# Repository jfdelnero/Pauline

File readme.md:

# Pauline FDC

Pauline is an open-source, powerful, universal and simple to use tool that will allow you to scan with
precision the content of the magnetic disks you want to archive, regardless of their format.

Pauline is a tool developed within the association La Ludothe`que Française, in partnership with
the associations Game Preservation Society located in Japan, and MO5.COM located in France.

https://www.laludotheque.fr/projets-en-cours/preservation-des-disquettes-pauline/

### Features

 - Based on the FPGA DE10-nano board.
 - Supports 8",5"1/4 3"1/2, 3" Shugart and PC drives.
 - Supports Apple II floppy drives.
 - Supports Macintosh floppy drives.
 - Capture resolution : 50 MHz or 25 MHz
 - Can capture up to 16 channels.
 - Can perfectly simulate/emulate up to 4 Shugart/PC drives (Mac/Apple II support planned)
 - Hardware drives emulation - No software or flash latency.
 - Based on Linux.
 - Embedded SSH / HTTP / FTP / Windows share servers.
 - USB and Ethernet connection.
 - Embedded web server to control the unit. No software to install on the computer.
 - Real time track analysis and display.

 And many more !

### How to build it ?

This use the HxCFloppyEmulator software repository as submodule so the proper way to clone the project is :

```c
git clone --recursive https://github.com/jfdelnero/Pauline.git
```

To update the repository :

```c
git pull
git submodule update --init --recursive
```

-------------------------------------------------------------------------------

HxC Floppy Emulator project

Generic/universal floppy disk drive emulators

Copyright (C) 2006-2026  Jean-François DEL NERO / HxC2001

Email :    hxc2001(at)hxc2001.com

Website :  https://hxc2001.com
           http://hxc2001.free.fr/floppy_drive_emulator

Forum :    https://torlus.com/floppy/forum

Facebook : https://www.facebook.com/groups/hxc2001/

Twitter :  https://twitter.com/jfdelnero

-------------------------------------------------------------------------------

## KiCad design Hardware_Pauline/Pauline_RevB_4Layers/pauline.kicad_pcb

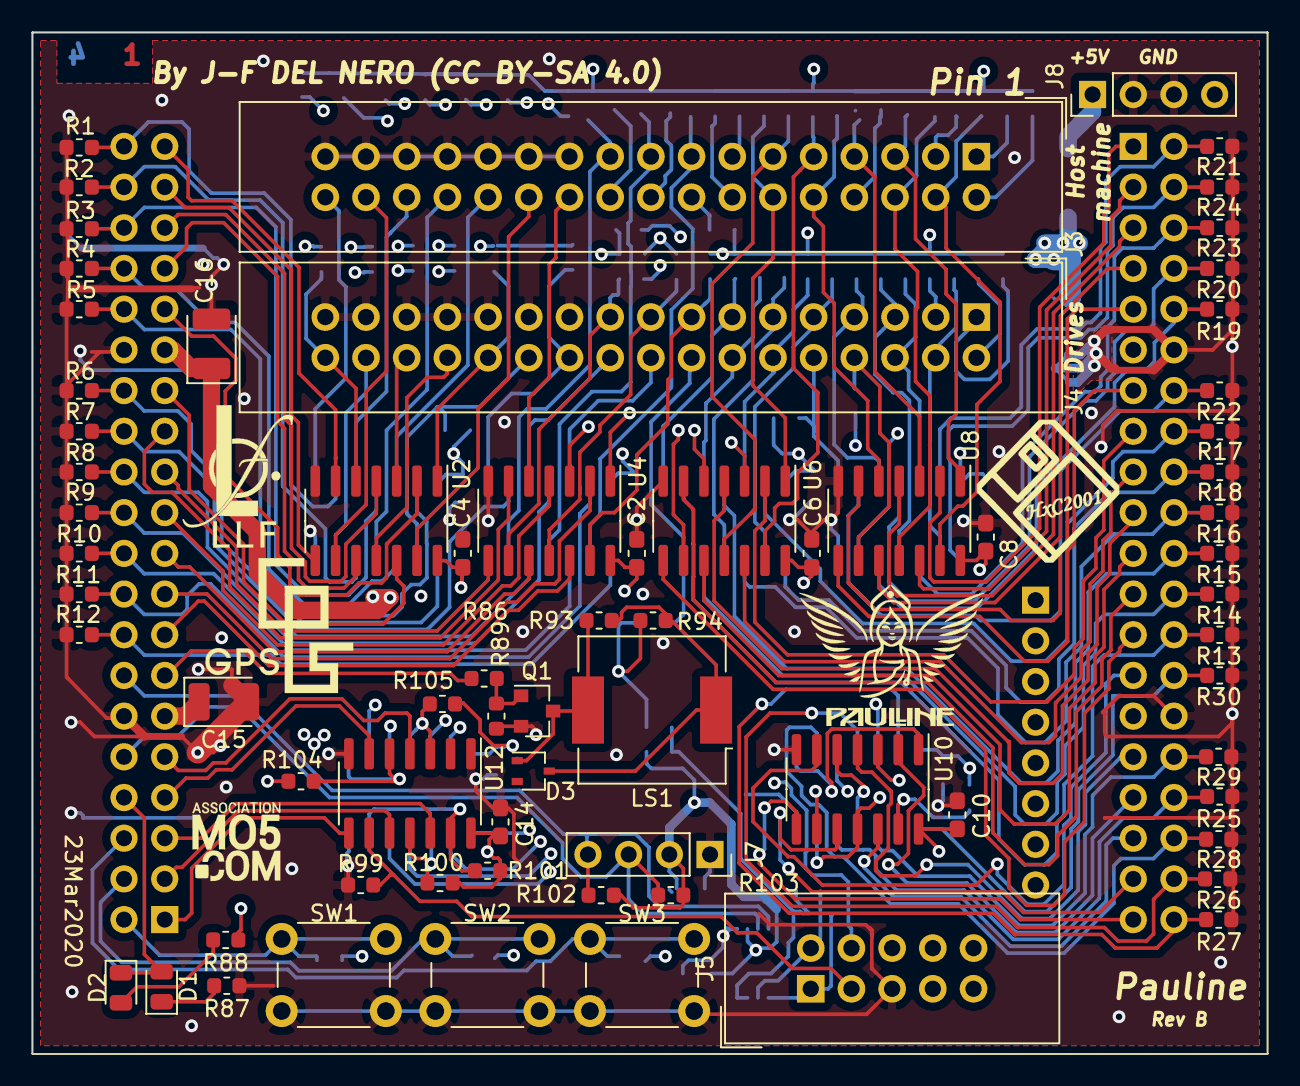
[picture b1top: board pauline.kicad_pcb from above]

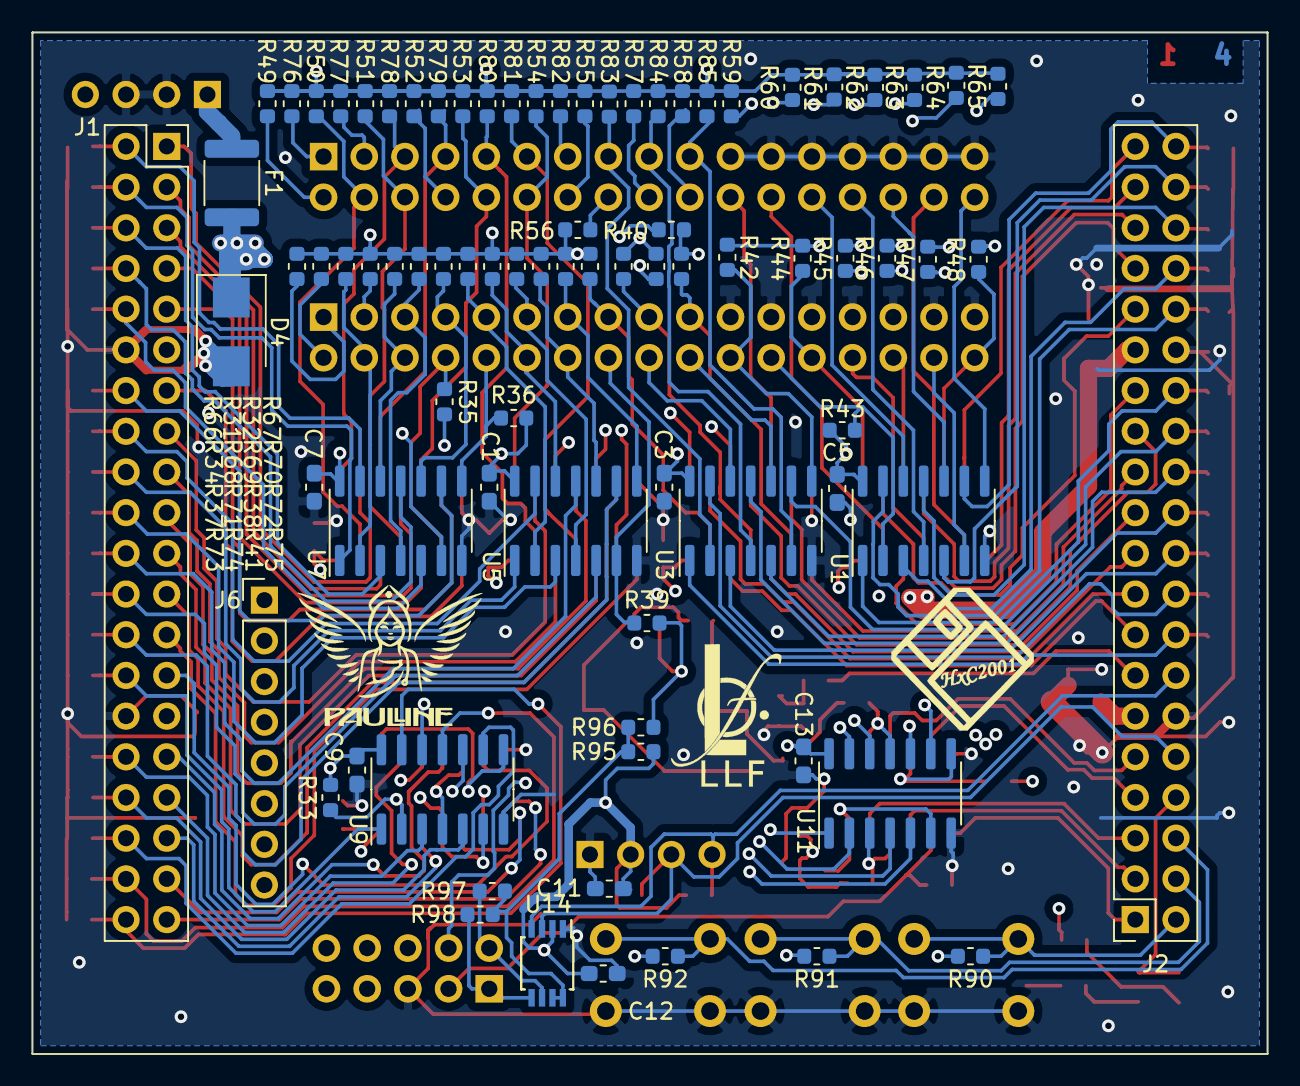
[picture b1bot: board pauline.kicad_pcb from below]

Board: 4 copper layers, 77.1 x 63.8 mm, 152 parts (82 on the bottom side), 152 nets.

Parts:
C1, C2, C3, C4, C5, C6, C7, C8, C9, C10, C11, C12, C13, C14: 100nF; C_0603_1608Metric_Pad1.05x0.95mm_HandSolder
C15, C16: 100uF; CP_EIA-3528-21_Kemet-B
D1: 0805 CMS RED LED; LED_0805_2012Metric
D2: 0805 CMS GREEN LED; LED_0805_2012Metric
D3: BAS16W; SOT-323_SC-70
D4: SMBJ5.0A; D_SMB
F1: Littelfuse 1812L260SLPR; Fuse_1812_4532Metric
J1, J2: ESW-120-33-T-D; PinSocket_2x20_P2.54mm_Vertical
J3, J4: Wurth 61203421621; IDC-Header_2x17_P2.54mm_Vertical
J5: HIF3FC-10PA-2.54DSA; IDC-Header_2x05_P2.54mm_Vertical
J6: Amphenol FCI 10129378-908001BLF; PinHeader_1x08_P2.54mm_Vertical
J7: TE Connectivity 5-534237-2 REC 1X04P; PinSocket_1x04_P2.54mm_Vertical
J8: Conn_01x04_Male; PinHeader_1x04_P2.54mm_Vertical
LS1: CPT-9019S-SMT-TR; Buzzer_CUI_CPT-9019S-SMT
Q1: BC817K-40HVL; SOT-23
R1, R2, R3, R4, R5, R6, R7, R8, R9, R10, R11, R12, R13, R14, R15, R16, R17, R18, R19, R20, R21, R22, R23, R24, R25, R26, R27, R28, R29, R30, R97, R98: 2K2; R_0603_1608Metric
R31, R32, R33, R34, R35, R36, R37, R38, R39, R40, R41, R42, R43, R44, R45, R46, R47, R48, R49, R50, R51, R52, R53, R54, R55, R56, R57, R58, R59, R60, R61, R62, R63, R64, R65, R66, R67, R68, R69, R70, R71, R72, R73, R74, R75, R76, R77, R78, R79, R80, R81, R82, R83, R84, R85, R86, R89, R90, R91, R92, R93, R99, R100, R101, R102, R103, R104, R105: 1K; R_0603_1608Metric
R87, R88: 150R; R_0603_1608Metric
R94, R95, R96: 0R; R_0603_1608Metric
SW1, SW2, SW3: Schurter 693-1301.9302; SW_PUSH_6mm
U1, U3, U5, U7, U9: SN74LS06D; SOIC-14_3.9x8.7mm_P1.27mm
U2, U4, U6, U8, U10, U12: MC74LVX14DR2G; SOIC-14_3.9x8.7mm_P1.27mm
U11: 74LCX125MX; SOIC-14_3.9x8.7mm_P1.27mm
U14: PCA9306; TSSOP-8_3x3mm_P0.65mm

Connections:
+3V3: C2.1, C4.1, C6.1, C8.1, C10.1, C11.1, C12.1, C13.1, C14.1, C16.1, J1.29, J2.29, J7.2, R88.1, R90.2, R91.2, R92.2, R95.2, R100.2, R101.2, R102.1, R103.1, R104.2, R105.2, U2.14, U4.14, U6.14, U8.14, U10.14, U11.14, U12.14, U14.2
+5V: C1.1, C3.1, C5.1, C7.1, C9.1, C15.1, D4.1, F1.1, J1.11, J2.11, J5.6, R31.2, R32.2, R33.2, R34.2, R35.2, R36.2, R37.2, R38.2, R39.2, R40.2, R41.2, R42.2, R43.2, R44.2, R45.2, R46.2, R47.2, R48.2, R49.2, R50.2, R51.2, R52.2, R53.2, R54.2, R55.2, R56.2, R57.2, R58.2, R59.2, R60.2, R61.2, R62.2, R63.2, R64.2, R65.2, R66.2, R67.2, R68.2, R69.2, R70.2, R71.2, R72.2, R73.2, R74.2, R75.2, R76.2, R77.2, R78.2, R79.2, R80.2, R81.2, R82.2, R83.2, R84.2, R85.2, R94.2, R96.2, U1.14, U3.14, U5.14, U7.14, U9.14
/Arduino_IO0: J6.8, U11.5
/Arduino_IO1: J6.7, U11.4
/Arduino_IO2: J6.6, U11.2
/Arduino_IO3: J6.5, U11.1
/Arduino_IO4: J6.4, U11.13
/Arduino_IO5: J6.3, U11.12
/Arduino_IO6: J6.2, U11.10
/Arduino_IO7: J6.1, U11.9
/EXT_I2C_SCL: J5.2, R97.1, U14.6
/EXT_I2C_SDA: J5.1, R98.1, U14.5
/EXT_INT: J5.3, R99.2, U12.9
/EXT_IO: J5.4, R33.1, U9.2, U10.13
/FLOPPY[1]: J4.1, R66.1, U9.10
/FLOPPY[2]: J4.2, R31.1, U9.12, U10.9
/FLOPPY[3]: J4.3, R67.1, U9.8, U10.1
/FLOPPY[4]: J4.4, R32.1, U7.2
/FLOPPY[5]: J4.5, R68.1, U7.4
/FLOPPY[6]: J4.6, R34.1, U7.12
/FLOPPY[7]: J4.7, R69.1, U7.10
/FLOPPY[8]: J4.8, R35.1, U8.9
/FLOPPY[9]: J4.9, R70.1, U5.2
/FLOPPY[10]: J4.10, R36.1, U7.8
/FLOPPY[11]: J4.11, R71.1, U5.4
/FLOPPY[12]: J4.12, R37.1, U5.12
/FLOPPY[13]: J4.13, R72.1, U5.8
/FLOPPY[14]: J4.14, R38.1, U5.10
/FLOPPY[15]: J4.15, R73.1, U4.13
/FLOPPY[16]: J4.16, R39.1, U5.6
/FLOPPY[17]: J4.17, R74.1, U4.11
/FLOPPY[18]: J4.18, R40.1, U3.12
/FLOPPY[19]: J4.19, R75.1, U4.9
/FLOPPY[20]: J4.20, R41.1, U3.10
/FLOPPY[22]: J4.22, R42.1, U3.8
/FLOPPY[24]: J4.24, R43.1, U1.2
/FLOPPY[26]: J4.26, R44.1, U2.1
/FLOPPY[28]: J4.28, R45.1, U2.11
/FLOPPY[30]: J4.30, R46.1, U2.3
/FLOPPY[32]: J4.32, R47.1, U1.6
/FLOPPY[34]: J4.34, R48.1, U2.5
/GPIO_0[0]: J1.1, U8.2
/GPIO_0[1]: J1.2, R21.1, U7.13
/GPIO_0[2]: J1.3, U8.12
/GPIO_0[3]: J1.4, R24.1, U7.1
/GPIO_0[4]: J1.5, U8.4
/GPIO_0[5]: J1.6, R23.1, U7.3
/GPIO_0[6]: J1.7, U8.10
/GPIO_0[7]: J1.8, R20.1, U7.11
/GPIO_0[8]: J1.9, U8.6
/GPIO_0[9]: J1.10, R19.1, U7.5
/GPIO_0[10]: J1.13, U8.8
/GPIO_0[11]: J1.14, R22.1, U7.9
/GPIO_0[12]: J1.15, U6.2
/GPIO_0[13]: J1.16, R17.1, U5.13
/GPIO_0[14]: J1.17, U6.12
/GPIO_0[15]: J1.18, R18.1, U5.1
/GPIO_0[16]: J1.19, U6.4
/GPIO_0[17]: J1.20, R16.1, U5.3
/GPIO_0[18]: J1.21, U6.10
/GPIO_0[19]: J1.22, R15.1, U5.11
/GPIO_0[20]: J1.23, U6.6
/GPIO_0[21]: J1.24, R14.1, U5.5
/GPIO_0[22]: J1.25, U6.8
/GPIO_0[23]: J1.26, R13.1, U5.9
/GPIO_0[24]: J1.27, U10.6
/GPIO_0[25]: J1.28, R30.1, U9.1
/GPIO_0[26]: J1.31, U10.4
/GPIO_0[27]: J1.32, R29.1, U9.3
/GPIO_0[28]: J1.33, U10.2
/GPIO_0[29]: J1.34, R25.1, U9.5
/GPIO_0[30]: J1.35, U10.12
/GPIO_0[31]: J1.36, R28.1, U9.9
/GPIO_0[32]: J1.37, U10.10
/GPIO_0[33]: J1.38, R26.1, U9.11
/GPIO_0[34]: J1.39, U10.8
/GPIO_0[35]: J1.40, R27.1, U9.13
/GPIO_1[0]: J2.1, U12.8
/GPIO_1[1]: J2.2, R90.1, SW1.1
/GPIO_1[2]: J2.3, U12.10
/GPIO_1[3]: J2.4, R91.1, SW2.1
/GPIO_1[4]: J2.5, U12.12
/GPIO_1[5]: J2.6, R92.1, SW3.1
/GPIO_1[6]: J2.7, U12.6
/GPIO_1[7]: D1.2, D2.1, J2.8
/GPIO_1[8]: J2.9, U12.4
/GPIO_1[9]: J2.10, J7.3, R103.2, U14.3
/GPIO_1[10]: J2.13, R86.2
/GPIO_1[11]: J2.14, J7.4, R102.2, U14.4
/GPIO_1[12]: J2.15, U4.12
/GPIO_1[13]: J2.16, R12.1, U3.1
/GPIO_1[14]: J2.17, U4.2
/GPIO_1[15]: J2.18, R11.1, U3.13
/GPIO_1[16]: J2.19, U4.10
/GPIO_1[17]: J2.20, R10.1, U3.3
/GPIO_1[18]: J2.21, U4.4
/GPIO_1[19]: J2.22, R9.1, U3.11
/GPIO_1[20]: J2.23, U4.8
/GPIO_1[21]: J2.24, R8.1, U3.5
/GPIO_1[22]: J2.25, U4.6
/GPIO_1[23]: J2.26, R7.1, U3.9
/GPIO_1[24]: J2.27, U2.12
/GPIO_1[25]: J2.28, R6.1, U1.1
/GPIO_1[26]: J2.31, U2.2
/GPIO_1[27]: J2.32, R5.1, U1.13
/GPIO_1[28]: J2.33, U2.10
/GPIO_1[29]: J2.34, R4.1, U1.3
/GPIO_1[30]: J2.35, U2.4
/GPIO_1[31]: J2.36, R3.1, U1.11
/GPIO_1[32]: J2.37, U2.8
/GPIO_1[33]: J2.38, R2.1, U1.5
/GPIO_1[34]: J2.39, U2.6
/GPIO_1[35]: J2.40, R1.1, U1.9
/HOST[1]: J3.1, R76.1, U10.3
/HOST[2]: J3.2, R49.1, U9.6, U10.11
/HOST[3]: J3.3, R77.1, U9.4, U10.5
/HOST[4]: J3.4, R50.1, U8.13
/HOST[5]: J3.5, R78.1, U8.1
/HOST[6]: J3.6, R51.1, U8.11
/HOST[7]: J3.7, R79.1, U8.3
/HOST[8]: J3.8, R52.1, U7.6
/HOST[9]: J3.9, R80.1, U6.13
/HOST[10]: J3.10, R53.1, U8.5
/HOST[11]: J3.11, R81.1, U6.11
/HOST[12]: J3.12, R54.1, U6.1
/HOST[13]: J3.13, R82.1, U6.5
/HOST[14]: J3.14, R55.1, U6.3
/HOST[15]: J3.15, R83.1, U3.2
/HOST[16]: J3.16, R56.1, U6.9
/HOST[17]: J3.17, R84.1, U3.4
/HOST[18]: J3.18, R57.1, U4.1
/HOST[19]: J3.19, R85.1, U3.6
/HOST[20]: J3.20, R58.1, U4.3
/HOST[22]: J3.22, R59.1, U4.5
/HOST[24]: J3.24, R60.1, U2.13
/HOST[26]: J3.26, R61.1, U1.12
/HOST[28]: J3.28, R62.1, U1.4
/HOST[30]: J3.30, R63.1, U1.10
/HOST[32]: J3.32, R64.1, U2.9
/HOST[34]: J3.34, R65.1, U1.8
/TRIS_IO0: J5.7, R100.1, U11.3, U12.11
/TRIS_IO1: J5.8, R101.1, U11.6, U12.13
/TRIS_IO2: J5.9, R104.1, U11.8, U12.5
/TRIS_IO3: J5.10, R105.1, U11.11, U12.3
GND: C1.2, C2.2, C3.2, C4.2, C5.2, C6.2, C7.2, C8.2, C9.2, C10.2, C11.2, C12.2, C13.2, C14.2, C15.2, C16.2, D4.2, J1.12, J1.30, J2.12, J2.30, J3.21, J3.23, J3.25, J3.27, J3.29, J3.31, J3.33, J4.21, J4.23, J4.25, J4.27, J4.29, J4.31, J4.33, J5.5, J7.1, J8.2, J8.3, Q1.2, R1.2, R2.2, R3.2, R4.2, R5.2, R6.2, R7.2, R8.2, R9.2, R10.2, R11.2, R12.2, R13.2, R14.2, R15.2, R16.2, R17.2, R18.2, R19.2, R20.2, R21.2, R22.2, R23.2, R24.2, R25.2, R26.2, R27.2, R28.2, R29.2, R30.2, R87.1, R89.2, R99.1, SW1.2, SW2.2, SW3.2, U1.7, U2.7, U3.7, U4.7, U5.7, U6.7, U7.7, U8.7, U9.7, U10.7, U11.7, U12.1, U12.7, U14.1
unnamed: D1.1, R87.2
unnamed: D2.2, R88.2
unnamed: D3.1, LS1.2, Q1.3, R93.1
unnamed: D3.3, LS1.1, R93.2, R94.1
unnamed: F1.2, J8.1
unnamed: Q1.1, R86.1, R89.1
unnamed: R95.1, R96.1, R97.2, R98.2, U14.7, U14.8

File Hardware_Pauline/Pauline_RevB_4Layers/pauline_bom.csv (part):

Source:;/media/jeff/Data_fast/sourcesforges/HxCFloppyEmulator/Pauline/trunk/Hardware_Pauline/Pauline_RevB_4Layers/pauline.sch;;;;;;;
Date:;Mon 15 Jun 2020 10:51:51 PM CEST;;;;;;;
Tool:;Eeschema 5.1.6-c6e7f7d~86~ubuntu18.04.1;;;;;;;
Generator:;/usr/share/kicad/plugins/bom_csv_grouped_by_value.py;;;;;;;
Component Count:;152;;;;;;;

Individual Components:;;;;;;;;

Item;Qty;Reference(s);Value;LibPart;Footprint;Datasheet;NC;Remarks
;;C1;100nF;Device:C;Capacitor_SMD:C_0603_1608Metric_Pad1.05x0.95mm_HandSolder;~;;
;;C2;100nF;Device:C;Capacitor_SMD:C_0603_1608Metric_Pad1.05x0.95mm_HandSolder;~;;
;;C3;100nF;Device:C;Capacitor_SMD:C_0603_1608Metric_Pad1.05x0.95mm_HandSolder;~;;
;;C4;100nF;Device:C;Capacitor_SMD:C_0603_1608Metric_Pad1.05x0.95mm_HandSolder;~;;
;;C5;100nF;Device:C;Capacitor_SMD:C_0603_1608Metric_Pad1.05x0.95mm_HandSolder;~;;
;;C6;100nF;Device:C;Capacitor_SMD:C_0603_1608Metric_Pad1.05x0.95mm_HandSolder;~;;
;;C7;100nF;Device:C;Capacitor_SMD:C_0603_1608Metric_Pad1.05x0.95mm_HandSolder;~;;
;;C8;100nF;Device:C;Capacitor_SMD:C_0603_1608Metric_Pad1.05x0.95mm_HandSolder;~;;
;;C9;100nF;Device:C;Capacitor_SMD:C_0603_1608Metric_Pad1.05x0.95mm_HandSolder;~;;
;;C10;100nF;Device:C;Capacitor_SMD:C_0603_1608Metric_Pad1.05x0.95mm_HandSolder;~;;
;;C11;100nF;Device:C;Capacitor_SMD:C_0603_1608Metric_Pad1.05x0.95mm_HandSolder;~;;
;;C12;100nF;Device:C;Capacitor_SMD:C_0603_1608Metric_Pad1.05x0.95mm_HandSolder;~;;
;;C13;100nF;Device:C;Capacitor_SMD:C_0603_1608Metric_Pad1.05x0.95mm_HandSolder;~;;
;;C14;100nF;Device:C;Capacitor_SMD:C_0603_1608Metric_Pad1.05x0.95mm_HandSolder;~;;
;;C15;100uF;Device:CP;Capacitor_Tantalum_SMD:CP_EIA-3528-21_Kemet-B;~;;
;;C16;100uF;Device:CP;Capacitor_Tantalum_SMD:CP_EIA-3528-21_Kemet-B;~;;
;;D1;0805 CMS RED LED;Device:LED;LED_SMD:LED_0805_2012Metric;~;;
;;D2;0805 CMS GREEN LED;Device:LED;LED_SMD:LED_0805_2012Metric;~;;
;;D3;BAS16W;Diode:BAS16W;Package_TO_SOT_SMD:SOT-323_SC-70;https://assets.nexperia.com/documents/data-sheet/BAS16_SER.pdf;NC;
;;D4;SMBJ5.0A;Diode:1.5KExxA;Diode_SMD:D_SMB;https://www.vishay.com/docs/88301/15ke.pdf;;Possible placement issue - optional part - Don't mount it.
;;F1;Littelfuse 1812L260SLPR;Device:Polyfuse;Fuse:Fuse_1812_4532Metric;~;;optional part.
;;J1;ESW-120-33-T-D;Connector_Generic:Conn_02x20_Odd_Even;Connector_PinSocket_2.54mm:PinSocket_2x20_P2.54mm_Vertical;~;;
;;J2;ESW-120-33-T-D;Connector_Generic:Conn_02x20_Odd_Even;Connector_PinSocket_2.54mm:PinSocket_2x20_P2.54mm_Vertical;~;;
;;J3;Wurth 61203421621;Connector_Generic:Conn_02x17_Odd_Even;Connector_IDC:IDC-Header_2x17_P2.54mm_Vertical;~;;
;;J4;Wurth 61203421621;Connector_Generic:Conn_02x17_Odd_Even;Connector_IDC:IDC-Header_2x17_P2.54mm_Vertical;~;;
;;J5;HIF3FC-10PA-2.54DSA;Connector_Generic:Conn_02x05_Odd_Even;Connector_IDC:IDC-Header_2x05_P2.54mm_Vertical;~;;
;;J6;Amphenol FCI 10129378-908001BLF;Connector:Conn_01x08_Male;Connector_PinHeader_2.54mm:PinHeader_1x08_P2.54mm_Vertical;~;;
;;J7;TE Connectivity 5-534237-2 REC 1X04P;Connector:Conn_01x04_Male;Connector_PinSocket_2.54mm:PinSocket_1x04_P2.54mm_Vertical;~;;
;;J8;Conn_01x04_Male;Connector:Conn_01x04_Male;Connector_PinHeader_2.54mm:PinHeader_1x04_P2.54mm_Vertical;~;;
;;LS1;CPT-9019S-SMT-TR;Device:Speaker_Ultrasound;Buzzer_Beeper:Buzzer_CUI_CPT-9019S-SMT;~;;
;;Q1;BC817K-40HVL;Transistor_BJT:BC817;Package_TO_SOT_SMD:SOT-23;http://www.fairchildsemi.com/ds/BC/BC817.pdf;;
;;R1;2K2;Device:R;Resistor_SMD:R_0603_1608Metric;~;;
;;R2;2K2;Device:R;Resistor_SMD:R_0603_1608Metric;~;;
;;R3;2K2;Device:R;Resistor_SMD:R_0603_1608Metric;~;;
;;R4;2K2;Device:R;Resistor_SMD:R_0603_1608Metric;~;;
;;R5;2K2;Device:R;Resistor_SMD:R_0603_1608Metric;~;;
;;R6;2K2;Device:R;Resistor_SMD:R_0603_1608Metric;~;;
;;R7;2K2;Device:R;Resistor_SMD:R_0603_1608Metric;~;;
;;R8;2K2;Device:R;Resistor_SMD:R_0603_1608Metric;~;;
;;R9;2K2;Device:R;Resistor_SMD:R_0603_1608Metric;~
;;R10;2K2;Device:R;Resistor_SMD:R_0603_1608Metric;~
;;R11;2K2;Device:R;Resistor_SMD:R_0603_1608Metric;~
;;R12;2K2;Device:R;Resistor_SMD:R_0603_1608Metric;~
;;R13;2K2;Device:R;Resistor_SMD:R_0603_1608Metric;~
;;R14;2K2;Device:R;Resistor_SMD:R_0603_1608Metric;~
;;R15;2K2;Device:R;Resistor_SMD:R_0603_1608Metric;~
;;R16;2K2;Device:R;Resistor_SMD:R_0603_1608Metric;~
;;R17;2K2;Device:R;Resistor_SMD:R_0603_1608Metric;~
;;R18;2K2;Device:R;Resistor_SMD:R_0603_1608Metric;~
;;R19;2K2;Device:R;Resistor_SMD:R_0603_1608Metric;~
;;R20;2K2;Device:R;Resistor_SMD:R_0603_1608Metric;~
;;R21;2K2;Device:R;Resistor_SMD:R_0603_1608Metric;~
;;R22;2K2;Device:R;Resistor_SMD:R_0603_1608Metric;~
;;R23;2K2;Device:R;Resistor_SMD:R_0603_1608Metric;~
;;R24;2K2;Device:R;Resistor_SMD:R_0603_1608Metric;~
;;R25;2K2;Device:R;Resistor_SMD:R_0603_1608Metric;~
;;R26;2K2;Device:R;Resistor_SMD:R_0603_1608Metric;~
;;R27;2K2;Device:R;Resistor_SMD:R_0603_1608Metric;~
;;R28;2K2;Device:R;Resistor_SMD:R_0603_1608Metric;~
;;R29;2K2;Device:R;Resistor_SMD:R_0603_1608Metric;~
;;R30;2K2;Device:R;Resistor_SMD:R_0603_1608Metric;~
;;R31;1K;Device:R;Resistor_SMD:R_0603_1608Metric;~
;;R32;1K;Device:R;Resistor_SMD:R_0603_1608Metric;~
;;R33;1K;Device:R;Resistor_SMD:R_0603_1608Metric;~
;;R34;1K;Device:R;Resistor_SMD:R_0603_1608Metric;~
;;R35;1K;Device:R;Resistor_SMD:R_0603_1608Metric;~
;;R36;1K;Device:R;Resistor_SMD:R_0603_1608Metric;~
;;R37;1K;Device:R;Resistor_SMD:R_0603_1608Metric;~
;;R38;1K;Device:R;Resistor_SMD:R_0603_1608Metric;~
;;R39;1K;Device:R;Resistor_SMD:R_0603_1608Metric;~
;;R40;1K;Device:R;Resistor_SMD:R_0603_1608Metric;~
;;R41;1K;Device:R;Resistor_SMD:R_0603_1608Metric;~
;;R42;1K;Device:R;Resistor_SMD:R_0603_1608Metric;~
;;R43;1K;Device:R;Resistor_SMD:R_0603_1608Metric;~
;;R44;1K;Device:R;Resistor_SMD:R_0603_1608Metric;~
;;R45;1K;Device:R;Resistor_SMD:R_0603_1608Metric;~
;;R46;1K;Device:R;Resistor_SMD:R_0603_1608Metric;~
;;R47;1K;Device:R;Resistor_SMD:R_0603_1608Metric;~
;;R48;1K;Device:R;Resistor_SMD:R_0603_1608Metric;~
;;R49;1K;Device:R;Resistor_SMD:R_0603_1608Metric;~
;;R50;1K;Device:R;Resistor_SMD:R_0603_1608Metric;~
;;R51;1K;Device:R;Resistor_SMD:R_0603_1608Metric;~
;;R52;1K;Device:R;Resistor_SMD:R_0603_1608Metric;~
;;R53;1K;Device:R;Resistor_SMD:R_0603_1608Metric;~
;;R54;1K;Device:R;Resistor_SMD:R_0603_1608Metric;~
;;R55;1K;Device:R;Resistor_SMD:R_0603_1608Metric;~
;;R56;1K;Device:R;Resistor_SMD:R_0603_1608Metric;~
;;R57;1K;Device:R;Resistor_SMD:R_0603_1608Metric;~
;;R58;1K;Device:R;Resistor_SMD:R_0603_1608Metric;~
;;R59;1K;Device:R;Resistor_SMD:R_0603_1608Metric;~
;;R60;1K;Device:R;Resistor_SMD:R_0603_1608Metric;~
;;R61;1K;Device:R;Resistor_SMD:R_0603_1608Metric;~
;;R62;1K;Device:R;Resistor_SMD:R_0603_1608Metric;~
;;R63;1K;Device:R;Resistor_SMD:R_0603_1608Metric;~
;;R64;1K;Device:R;Resistor_SMD:R_0603_1608Metric;~
;;R65;1K;Device:R;Resistor_SMD:R_0603_1608Metric;~
;;R66;1K;Device:R;Resistor_SMD:R_0603_1608Metric;~
;;R67;1K;Device:R;Resistor_SMD:R_0603_1608Metric;~
;;R68;1K;Device:R;Resistor_SMD:R_0603_1608Metric;~
;;R69;1K;Device:R;Resistor_SMD:R_0603_1608Metric;~
;;R70;1K;Device:R;Resistor_SMD:R_0603_1608Metric;~
;;R71;1K;Device:R;Resistor_SMD:R_0603_1608Metric;~
;;R72;1K;Device:R;Resistor_SMD:R_0603_1608Metric;~
;;R73;1K;Device:R;Resistor_SMD:R_0603_1608Metric;~
;;R74;1K;Device:R;Resistor_SMD:R_0603_1608Metric;~
;;R75;1K;Device:R;Resistor_SMD:R_0603_1608Metric;~
;;R76;1K;Device:R;Resistor_SMD:R_0603_1608Metric;~
;;R77;1K;Device:R;Resistor_SMD:R_0603_1608Metric;~
;;R78;1K;Device:R;Resistor_SMD:R_0603_1608Metric;~
;;R79;1K;Device:R;Resistor_SMD:R_0603_1608Metric;~
;;R80;1K;Device:R;Resistor_SMD:R_0603_1608Metric;~
;;R81;1K;Device:R;Resistor_SMD:R_0603_1608Metric;~
;;R82;1K;Device:R;Resistor_SMD:R_0603_1608Metric;~
;;R83;1K;Device:R;Resistor_SMD:R_0603_1608Metric;~
;;R84;1K;Device:R;Resistor_SMD:R_0603_1608Metric;~
;;R85;1K;Device:R;Resistor_SMD:R_0603_1608Metric;~
;;R86;1K;Device:R;Resistor_SMD:R_0603_1608Metric;~
;;R87;150R;Device:R;Resistor_SMD:R_0603_1608Metric;~
;;R88;150R;Device:R;Resistor_SMD:R_0603_1608Metric;~
;;R89;1K;Device:R;Resistor_SMD:R_0603_1608Metric;~;
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
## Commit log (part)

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2020-04-20 Pauline : Linux build scripts.
2020-04-20 Set exec flag.
2020-04-20 openssl url updated.
2020-04-21 Pauline control software.
2020-04-23 Pauline FPGA.
2020-04-27 OLED driver/library.
2020-04-27 Pauline tools and oled splash screen build.
2020-04-27 uboot preloader/loader sources.
2020-04-27 clean script.
2020-04-27 change the uboot archive format.
2020-04-28 Pauline build instructions.
2020-04-28 Some path fixes and rename.
2020-04-28 Board infos.
2020-04-28 More path and others fixes.
2020-04-28 exec flag set.
2020-04-28 dd : add sync.
2020-04-29 cmake build script.
2020-04-30 LibPNG + LibGD
2020-04-30 libgd libpng moved to the graphic stack.
2020-05-01 Samba build.
2020-05-01 samba and some others stuff.
2020-05-01 Samba share is working.
2020-05-02 ramdisk enabled. data partition auto init / format. partitions size adjusted.
2020-05-03 SH1106 / SSD1306 framebuffer driver.
2020-05-03 OLED dts.
2020-05-04 New splash tool.
2020-05-04 replaced by splash screen.
2020-05-04 Some splash screen bitmaps.
2020-05-04 new splash screens deployed.
2020-05-06 printf typo.
2020-05-06 home folder option.
2020-05-06 Dump : Automatic folder / index naming.
2020-05-06 more screen messages.
2020-05-06 Merging with the latest version.
2020-05-06 home folder set to /home/pauline.
2020-05-07 common sh1106 & ssd1306 compatible init/configuration.
2020-05-07 fix Windows 10 >=SMB2 and no guest requirements.
2020-05-07 remove comment and name end of line white space.
2020-05-10 Better work/home folder tree.
2020-05-10 Better work/home folder tree. cross compiled hxc tool added.
2020-05-10 WIP: screen printf functions.
2020-05-12 screen printf : center feature.
2020-05-12 Screen : Track position
2020-05-21 WIP : AP wifi support.
2020-05-22 fixing memory leak.
2020-05-22 Transparent mode + negative mode. print date.
2020-05-22 Print ethernet IP.
2020-05-22 Print date/hour and IP while waiting for a first connection.
2020-05-22 WIP : Pauline embedded control pages.
2020-05-22 fix pauline logo.
2020-05-22 svg->png
2020-05-22 typo.
2020-05-24 Fix i2c communication with some OLed screens.
2020-05-24 reduce the i2c slew rate and max current.
2020-05-24 ;Pauline Schematic and PCB Rev B.
2020-05-26 CC BY-SA 4.0 license.
2020-05-28 check for possible buffer overrun.
2020-05-28 build the hxc lib first.
2020-06-15 BOM : fix datasheet url.
2020-06-15 Pauline Rev B BOM.
2020-06-15 J1/J2/J6 connectors mounting.
2020-06-15 add pictures name in the remarks.
2020-06-30 Now auto-detect the SH1106 screens and set the right segment offset automatically.
2020-06-30 let the driver set the segment-offset automatically.
2020-06-30 Only update the screen when needed.
2020-07-02 multiples drives support. script support. various fixes.
2020-07-02 libhxcfe.so installation.
2020-07-02 fix target libhxcfe.so link.
2020-07-03 Add more IOs name aliases.
2020-07-03 More explanations.
2020-07-03 one more alias.
2020-07-03 Max steps drive protection.
2020-07-04 execute the default script.
2020-07-04 FLOPPY_DUMP_* changed to DRIVES_PORT_*
2020-07-04 fix script installation/update.
2020-07-06 twisted ribbon aliases.
2020-07-06 more io pins. set/clear/ioslist commands.
2020-07-06 x68000 eject support.
2020-07-07 eject disk : fix the return code.
2020-07-14 inotify drives autodetect head calibration max tracks detection.
2020-07-18 Replace Nexperia/nxp 74LVC06AD buffers by standard TTL 74LS06D buffers.
2020-07-18 modifications notes.
2020-07-20 Fix Settings folder initial installation.
2020-07-21 schematic pdf updated.
2020-07-23 Basic websocket library.
2020-07-23 Link against wsServer.
2020-07-23 WIP : websocket interface.
2020-07-23 websocket lib, update initrd.
2020-07-28 WIP : multi-clients support.
2020-07-29 WIP : websockets, multi-clients support.
2020-07-30 WIP : websockets, multi-clients support. (Debugging...)
2020-07-30 Connect the script/command layer to the new communication hub.
2020-07-30 X68000 select lines options.
2020-07-30 "system" command.
2020-07-30 pauline page : websocket interface enabled.
2020-07-31 costs estimation.
2020-08-11 new pauline control pages
2020-08-11 new pauline control pages : some fixes.
2020-08-12 fix disconnection - connection event.
2020-08-12 fix client connection status.
2020-08-12 Track dump lenght (ms) and Index to dump delay (ms) parameters.
2020-08-12 network data stream : multi clients support.
2020-08-16 J1,J2 reference changed to ESW-120-33-T-D.
2020-08-18 wsServer : Binary frame support, multi-ports support.
2020-08-18 WIP : websocket updated image.
2020-08-19 websocket floppy analysis image.
2020-08-24 WIP : More meta-data !
2020-08-24 some fixes and improvements.
2020-08-24 typo fix.
2020-08-24 unnecessary operation removed.
2020-08-24 more metadata. version code.
2020-08-24 graphique zoom sliders.
2020-08-24 ms -> us.
2020-08-25 drive reference, additional comments, operator fields. track preview : enable more controls.
2020-08-25 fix a memory leak in the png writer. fix compilation warnings.
2020-08-25 v1.1.1.2
2020-09-16 libhxcfe function renamed.
2020-10-05 help command : Drive Simulation select lines ID information.
2020-10-29 broadcast fix : only send packets to the clients connected to the same port.
2020-10-31 wsServer library updated.
2020-10-31 generic mux
2020-11-01 dump : can assign the signals to use during the dump. glitch filters can be set with registers ios expansion signals can be used during the dump. sound frequency generator added.
2020-11-01 mux dump support, sound support.
2020-11-01 check / fix user provided path/file name.
2020-11-01 error sound function.
2020-11-01 sound command.
2020-11-01 getio, sound commands added extio included in the dump.
2020-11-01 v1.1.0.0
2020-11-11 Disable the browsers cache.
2020-11-23 dump : end of stream fixed.
2020-11-23 wip : Apple I/II drive stepper motor control.
2020-11-24 move head & step commands : pass the double step status.
2020-11-24 head load support added, config file sound setting, double step behavior fixed.
2020-11-24 out signal polarity register extended.
2020-11-25 step width can be set.
2020-11-25 WIP: Apple Disk II interface mode/drive support.
2020-11-25 v1.2.1.1
2020-11-26 display rules.
2020-11-26 hxcfe moved.
2020-11-27 hxcfe_td_draw_trkstream : always draw the rules.
2020-11-28 fix apple drive/phases head step.
2020-11-28 Apple : Don't check the track 0 state.
2020-11-28 new dummy out port "UNCONNECTED_PORT_OUT".
2020-11-29 Step width registers.
2020-11-29 New parameters : Step width settings, index polarity, settling time... New commands : set/get parameters.
2020-11-29 command line banner : print the right version.
2020-12-07 populate the contact/about page.
2020-12-07 missing images removed, "under construction" image added
2020-12-18 wsServer updated.
2020-12-18 exception handler.
2020-12-18 crash logs file define.
2020-12-18 We can have more than 4 drives definitions.
2020-12-30 fix the preloader build.
2020-12-30 Apple : Be sure to recalibrate the head on the phase 0
2020-12-30 update url
2020-12-30 mailutils : disable python support.
2020-12-30 (c) date updated.
2021-01-18 v1.2.3.1
2021-01-18 C64, Victor 9000 and QuickDisk MO5 buttons.
2021-02-08 fix command line help.
2021-03-24 Linux update : GCC 10.2 and all others components updated.
2021-03-24 Macintosh drive support, interface mode configuration changed, gcc 10 support fixed.
2021-03-28 partition initialization : reboot right after the configuration.
2021-08-16 Drive simulation : pin 2 and pin 34 mode selection parameter / script command.
2021-08-16 v1.2.4.1
2021-08-16 fix some function names.
2021-08-16 (c) dates updated.
2021-09-02 wip : emulation, weak bits support.
2021-09-03 noise generator.
2021-09-05 fix dma stop address
2021-09-05 dump : fix the buffer size.
2021-09-05 leds output mux support external port floppy selection support.
2021-09-05 led1src & led2src options.
2021-09-05 remove binary.
2021-09-05 ledxsrc and help message fixed.
2021-09-06 Drive 1 and 2 leds.
2021-09-08 fix the write protect feature.
2021-09-09 floppy simulation/emulation write protect commands.
2021-10-23 Apple Macintosh : GCR / MFM mode selection support.
2021-11-12 floppy drives simulations : double step support.
2021-11-12 drive floppy drives simulations : double step support.
2021-12-18 Basic FM data separator.
2021-12-18 track : up / down mode support.
2021-12-18 drives : up down mode and data separator.
2021-12-18 hard sector index, up down step mode and data separator support.
2021-12-20 Data separator : The output signal can now be shaped to match with the requirements of different hardwares.
2021-12-20 fix single sided image support.
2021-12-24 scripts: fix possible function name conflict with the libhxcfe.
2021-12-24 enable usb over ethernet.
2021-12-24 increase the system disk size.
2021-12-24 enable valgrind.
2021-12-24 update valgrind.
2021-12-24 umtprd update
2021-12-24 composite usb configuration : rndis,ecm and mtp.
2021-12-26 fix USB configuration for Windows 10 support
2022-01-16 Data separator : Full clock/data separation mode support. (Memorex 651 Emulation)
2023-02-10 basic readme.md
2023-02-11 HxCFloppyEmulator submodule
2023-02-13 LFS scripts update.
2023-02-13 +x flags
2023-02-13 samba4 patches.
2023-02-13 iptables + libntp.
2023-02-13 common config update.
2023-02-13 target config.
2023-08-20 WIP : Pauline Linux BSP update.
2023-08-20 fix termlib/ncurses build.
2023-08-20 Build perl.
2023-08-20 fix.
2023-08-20 Parse-Yapp (Required by Samba...)
2023-08-27 Build host GCC.
2023-08-27 Samba build fix...
2023-08-27 build host gcc, and don't build heimdal anymore : use the samba embedded version.
2023-08-27 fix texinfo rebuild.
2023-08-27 possible buffer overrun fix.
2023-08-27 hxc soft update.
2023-08-27 readme update.
2023-08-27 white line.
2023-08-27 url fix.
2023-08-27 image creation into dev/shm
2023-08-28 get the kernel image.
2023-08-28 get the u-boot image.
2023-08-28 u-boot and kernel images should be already there.
2023-08-28 get u-boot mkimage
2023-08-28 remove temp folder.
2023-09-03 automatically set ALTERA_DE10_GHRD_BASEDIR.
2023-09-03 fix ssh keys permissions
2023-09-03 fix samba group
2023-09-03 call the generic fix permission script.1
2023-09-03 fix network settings.
2023-09-03 new samba config.
2023-09-03 enable haveged.
2023-09-03 ntp : faster sync
2023-09-04 openssl and openssh update.
2023-09-04 add some missing error checks.
2023-09-05 output_objects creation / deletion.
2023-09-05 check ALTERA_BASEDIR.
2023-09-05 clean-up temp folders.
2023-09-06 # u-boot is using "cc"
2023-09-06 cp -> ln
2023-09-09 Kernel 5.x/6.x support : Fixes + Workqueue usage
2023-09-09 Kernel 6.x support.
2023-09-09 FPGA bridges.
2023-09-09 Update to the most recent u-boot and kernel available.
2023-09-09 host ncurses is now build too.
2023-09-09 don't copy soc_system.dts to the image.
2023-09-10 wsServer update + multi ports support patch.
2023-09-10 wsServer update + fixes.
2023-09-10 fix possible string buffer overrun.
2023-09-10 generate some error messages.
2023-09-10 disable pxe service.
2023-09-12 fix : enable all hps<>fpga bridges.
2023-09-12 fix help page.
2023-09-12 more help
2023-09-12 floppy emulation -> image save : fix track size alignment.
2023-09-12 print fix.
2023-09-13 fix main versus hard sectors holes positions.
2023-09-13 hard sector and index length parameters.
2023-09-13 hard sector : move all indexes to align sectors to the track.
2023-09-13 remove unused operation.
2023-09-13 enable ddrescue.
2023-09-13 LIBJPEG
2023-09-13 enable usb camera / soundcard / wifi interface...
2023-09-14 more usb wifi interfaces support enabled.
2023-11-24 fix buffer size.
2024-02-08 openssh, openssl, zlib updated.

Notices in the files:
Hardware_Pauline/Pauline_RevB_4Layers/pauline.kicad_pcb:
By J-F DEL NERO (CC BY-SA 4.0)
